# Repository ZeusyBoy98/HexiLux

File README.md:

# HexiLux
Made for Hack Club Fallout.

## Zine

## What does it do?
A custom open-source smart lighting solution, using tiling hexagonal panels. Featuring music sync and home assistant compatibility. 

## Why/Motivation?
Because I enjoy DJing and music reactive lights to go behind my setup would be really cool and elevate my experience.

## How?
In order to make this project for yourself, you'll need to purchase/3D print the items in the bill of materials below.

| Quantity | Item               | URL                                                                                                                                                                                                                                    | Unit Price ($USD)   | Total Price ($USD)  |
| -------- | ------------------ | -------------------------------------------------------------------------------------------------------------------------------------------------------------------------------------------------------------------------------------- | ------------------- | ------------------- |
| 1        | Microphone         | [Zaitronics](https://zaitronics.com.au/products/inmp441-i2s-mems-omnidirectional-microphone?variant=51395922100516&country=AU&currency=AUD&utm_medium=product_sync&utm_source=google&utm_content=sag_organic&utm_campaign=sag_organic) | 5.57                | 5.57                |
| 3        | Neopixel (10 pack) | [DigiKey](https://www.digikey.com.au/en/products/detail/adafruit-industries-llc/1655/5154679)                                                                                                                                          | 4.50                | 13.50               |
| 1        | Button             | [DigiKey](https://www.digikey.com.au/en/products/detail/omron-electronics-inc-emc-div/B3F-4050/95200)                                                                                                                                  | 0.52                | 0.52                |
| 1        | Board<br>          | [DigiKey](https://www.digikey.com.au/en/products/detail/seeed-technology-co-ltd/113991114/19285530)                                                                                                                                    | 7.49                | 7.49                |
| 4        | 100nF Capacitor    | [DigiKey](https://www.digikey.com.au/en/products/detail/vishay-beyschlag-draloric-bc-components/K104K15X7RF5TL2/286538)                                                                                                                | 0.28                | 1.12                |
| 1        | 330 Resistor       | [DigiKey](https://www.digikey.com.au/en/products/detail/yageo/FMP200JR-52-330R/2058682)                                                                                                                                                | 0.19                | 0.19                |
| 1        | 10k Resistor       | [DigiKey](https://www.digikey.com.au/en/products/detail/yageo/FMP200JR-52-10K/2058646)                                                                                                                                                 | 0.19                | 0.19                |
| 2        | 5.1k Resistor      | [DigiKey](https://www.digikey.com.au/en/products/detail/yageo/RC0603FR-075K1L/727268)                                                                                                                                                  | 0.10                | 0.20                |
| 1        | 47uF Capacitor     | [DigiKey](https://www.digikey.com.au/en/products/detail/tdk/FK20X5R0J476MN000/2815373)                                                                                                                                                 | 0.86                | 0.86                |
| 1        | 100uF Capacitor    | [DigiKey](https://www.digikey.com.au/en/products/detail/murata-electronics/GRM31CD80J107MEA8L/13904781)                                                                                                                                | 0.44                | 0.44                |
| 1        | Level Shifter      | [DigiKey](https://www.digikey.com.au/en/products/detail/texas-instruments/SN74AHCT1G125DBVR/376028)                                                                                                                                    | 0.14                | 0.14                |
| 1        | USBC               | [DigiKey](https://www.digikey.com.au/en/products/detail/amphenol-cs-fci/10155435-00011LF/11602060)                                                                                                                                     | 0.85                | 0.85                |
|          | Case               | 3D print files in /CAD                                                                                                                                                                                                                 | (3D printing: 1.17) | (3D printing: 1.17) |
| PCB      |                    |                                                                                                                                                                                                                                        |                     | 29.24               |
| Shipping |                    |                                                                                                                                                                                                                                        |                     | 3.70+20+9.52=33.22  |
| Total    |                    |                                                                                                                                                                                                                                        |                     | 93.53               |

### Build Guide:

#### 1. Preparation
Before starting, make sure you have:
<ul>
<li>All components from the BOM
<li>A soldering iron + solder
<li>Tweezers (there are lots of small components)
<li>Flux (helpful)
<li>A 3D printer (or get the printed parts from someone else)
<li>A USB-C cable
<li>A USB-C power adapter
</ul>

#### 2. Soldering
Take your pcb and begin soldering components to it<br>
Wiring schematic:

Recommended order:
<ul>
<li>SMD Components (resistors/capacitors, neopixels, logic converters)
<li>Microcontroller (Seeed XIAO ESP32-S3)
<li>Through-hole components (resistors/capacitors, buttons, microphone)
</ul>

#### 3. Case
<ul>
<li>3D print the case bottom and top.
<li>Place the PCB into the case bottom
<li>Snap on the case top
</ul>

#### 4. Firmware
<ul>
<li>Plug the middle USB-C port (ESP32-S3) into a computer
<li>Go to https://install.wled.me/
<li>Install the WLED firmware to the board
<li>Unplug
<li>Plug a power adapter into the off-centre USB-C port
<li>Follow the instructions here to start using: https://kno.wled.ge/basics/getting-started/
</ul>

Enjoy your HexiLux panel!

## Renders

## Designing

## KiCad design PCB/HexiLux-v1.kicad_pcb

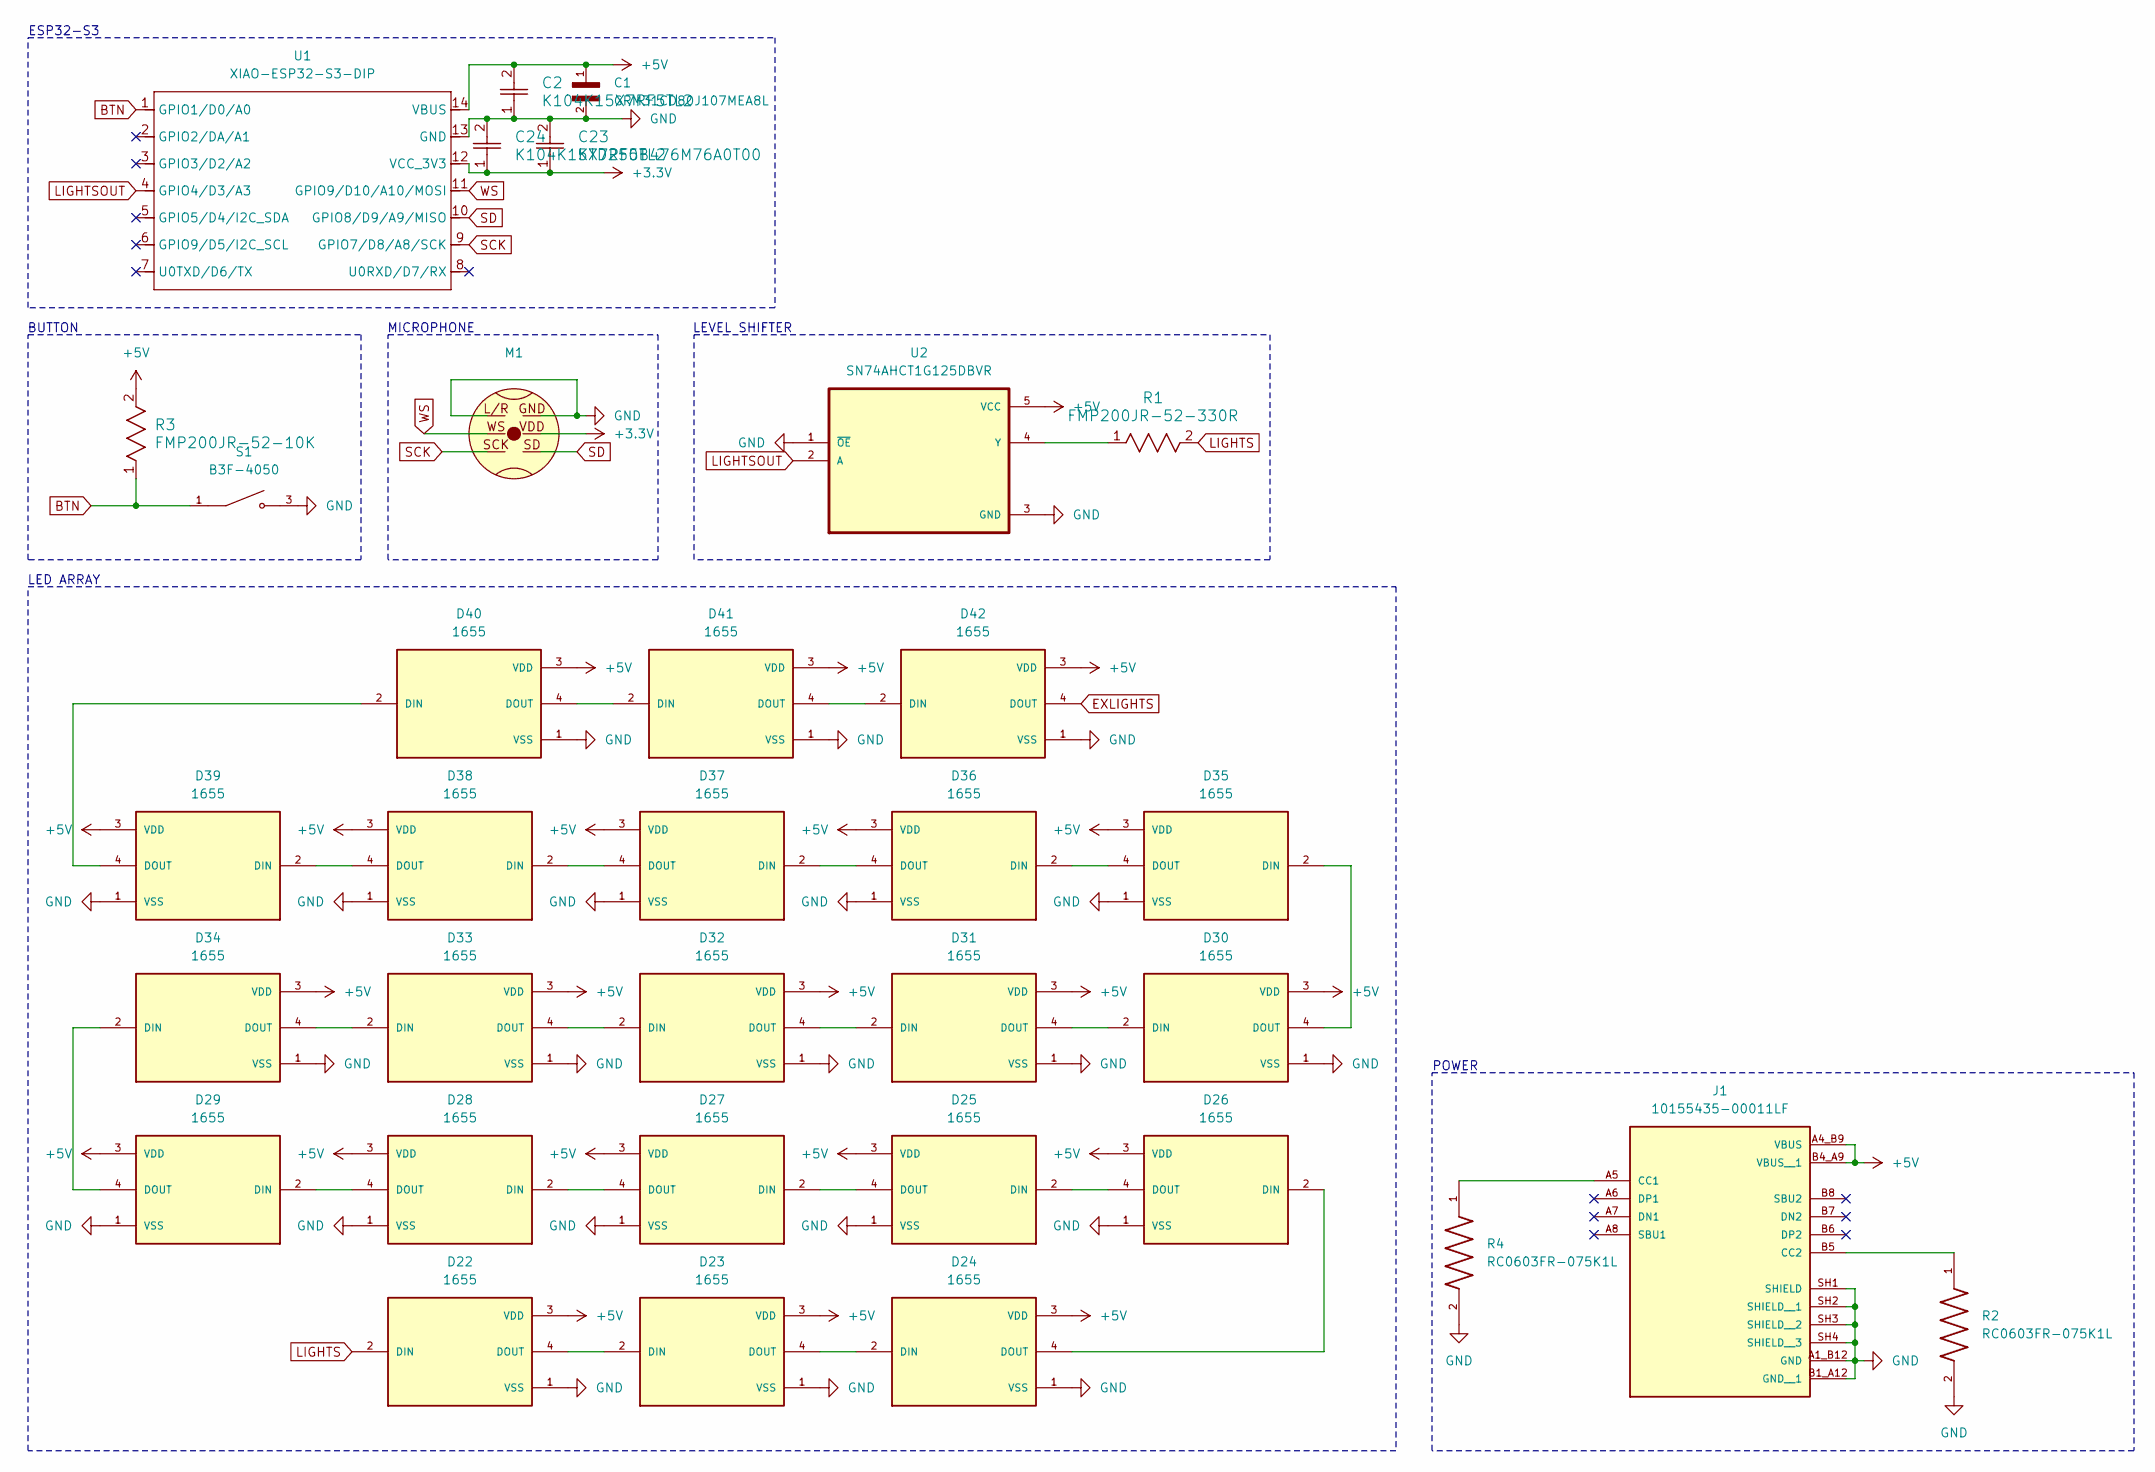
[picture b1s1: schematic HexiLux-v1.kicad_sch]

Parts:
C1: GRM31CD80J107MEA8L; 100uf_5V_1206; DigiKey_Part_Number 490-GRM31CD80J107MEA8LCT-ND
C2, C24: K104K15X7RF5TL2; K104K15X7RF5TL2_VIS
C23: KTD250B476M76A0T00; CAP_NTD_76_05.5T_NIP
D22, D23, D24, D25, D26, D27, D28, D29, D30, D31, D32, D33, D34, D35, D36, D37, D38, D39, D40, D41, D42: 1655; LED_1655_5050_neopixel; PARTREV 01
J1: 10155435-00011LF; AMPHENOL_10155435-00011LF; PARTREV C
M1: INMP441
R1: FMP200JR-52-330R; YAG_FMP200_YAG_52_330k
R2, R4: RC0603FR-075K1L; 5.1k_0603_DK
R3: FMP200JR-52-10K; YAG_FMP200_YAG
S1: B3F-4050; SW_B3F-4050; DigiKey_Part_Number SW413-ND
U1: XIAO-ESP32-S3-DIP
U2: SN74AHCT1G125DBVR; 74AHCT_level_shifter

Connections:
+3.3V: C23.1, C24.1, M1.VDD, U1.12 (VCC_3V3)
+5V: C1.1, C2.2, D22.3 (VDD), D23.3 (VDD), D24.3 (VDD), D25.3 (VDD), D26.3 (VDD), D27.3 (VDD), D28.3 (VDD), D29.3 (VDD), D30.3 (VDD), D31.3 (VDD), D32.3 (VDD), D33.3 (VDD), D34.3 (VDD), D35.3 (VDD), D36.3 (VDD), D37.3 (VDD), D38.3 (VDD), D39.3 (VDD), D40.3 (VDD), D41.3 (VDD), D42.3 (VDD), J1.A4_B9 (VBUS), J1.B4_A9 (VBUS__1), R3.2, U1.14 (VBUS), U2.5 (VCC)
BTN: R3.1, S1.1, S1.2, U1.1 (GPIO1/D0/A0)
EXLIGHTS: D42.4 (DOUT)
GND: C1.2, C2.1, C23.2, C24.2, D22.1 (VSS), D23.1 (VSS), D24.1 (VSS), D25.1 (VSS), D26.1 (VSS), D27.1 (VSS), D28.1 (VSS), D29.1 (VSS), D30.1 (VSS), D31.1 (VSS), D32.1 (VSS), D33.1 (VSS), D34.1 (VSS), D35.1 (VSS), D36.1 (VSS), D37.1 (VSS), D38.1 (VSS), D39.1 (VSS), D40.1 (VSS), D41.1 (VSS), D42.1 (VSS), J1.A1_B12 (GND), J1.B1_A12 (GND__1), J1.SH1 (SHIELD), J1.SH2 (SHIELD__1), J1.SH3 (SHIELD__2), J1.SH4 (SHIELD__3), M1.GND, M1.L/R, R2.2, R4.2, S1.3, S1.4, U1.13 (GND), U2.1 (~OE), U2.3 (GND)
LIGHTS: D22.2 (DIN), R1.2
LIGHTSOUT: U1.4 (GPIO4/D3/A3), U2.2 (A)
unnamed: D22.4 (DOUT), D23.2 (DIN)
unnamed: D23.4 (DOUT), D24.2 (DIN)
unnamed: D24.4 (DOUT), D26.2 (DIN)
unnamed: D25.2 (DIN), D26.4 (DOUT)
unnamed: D25.4 (DOUT), D27.2 (DIN)
unnamed: D27.4 (DOUT), D28.2 (DIN)
unnamed: D28.4 (DOUT), D29.2 (DIN)
unnamed: D29.4 (DOUT), D34.2 (DIN)
unnamed: D30.2 (DIN), D31.4 (DOUT)
unnamed: D30.4 (DOUT), D35.2 (DIN)
unnamed: D31.2 (DIN), D32.4 (DOUT)
unnamed: D32.2 (DIN), D33.4 (DOUT)
unnamed: D33.2 (DIN), D34.4 (DOUT)
unnamed: D35.4 (DOUT), D36.2 (DIN)
unnamed: D36.4 (DOUT), D37.2 (DIN)
unnamed: D37.4 (DOUT), D38.2 (DIN)
unnamed: D38.4 (DOUT), D39.2 (DIN)
unnamed: D39.4 (DOUT), D40.2 (DIN)
unnamed: D40.4 (DOUT), D41.2 (DIN)
unnamed: D41.4 (DOUT), D42.2 (DIN)
unnamed: J1.A5 (CC1), R4.1
unnamed: J1.B5 (CC2), R2.1
unnamed: R1.1, U2.4 (Y)
SCK: M1.SCK, U1.9 (GPIO7/D8/A8/SCK)
SD: M1.SD, U1.10 (GPIO8/D9/A9/MISO)
WS: M1.WS, U1.11 (GPIO9/D10/A10/MOSI)

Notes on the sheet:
POWER
LED ARRAY
BUTTON
MICROPHONE
ESP32-S3
LEVEL SHIFTER

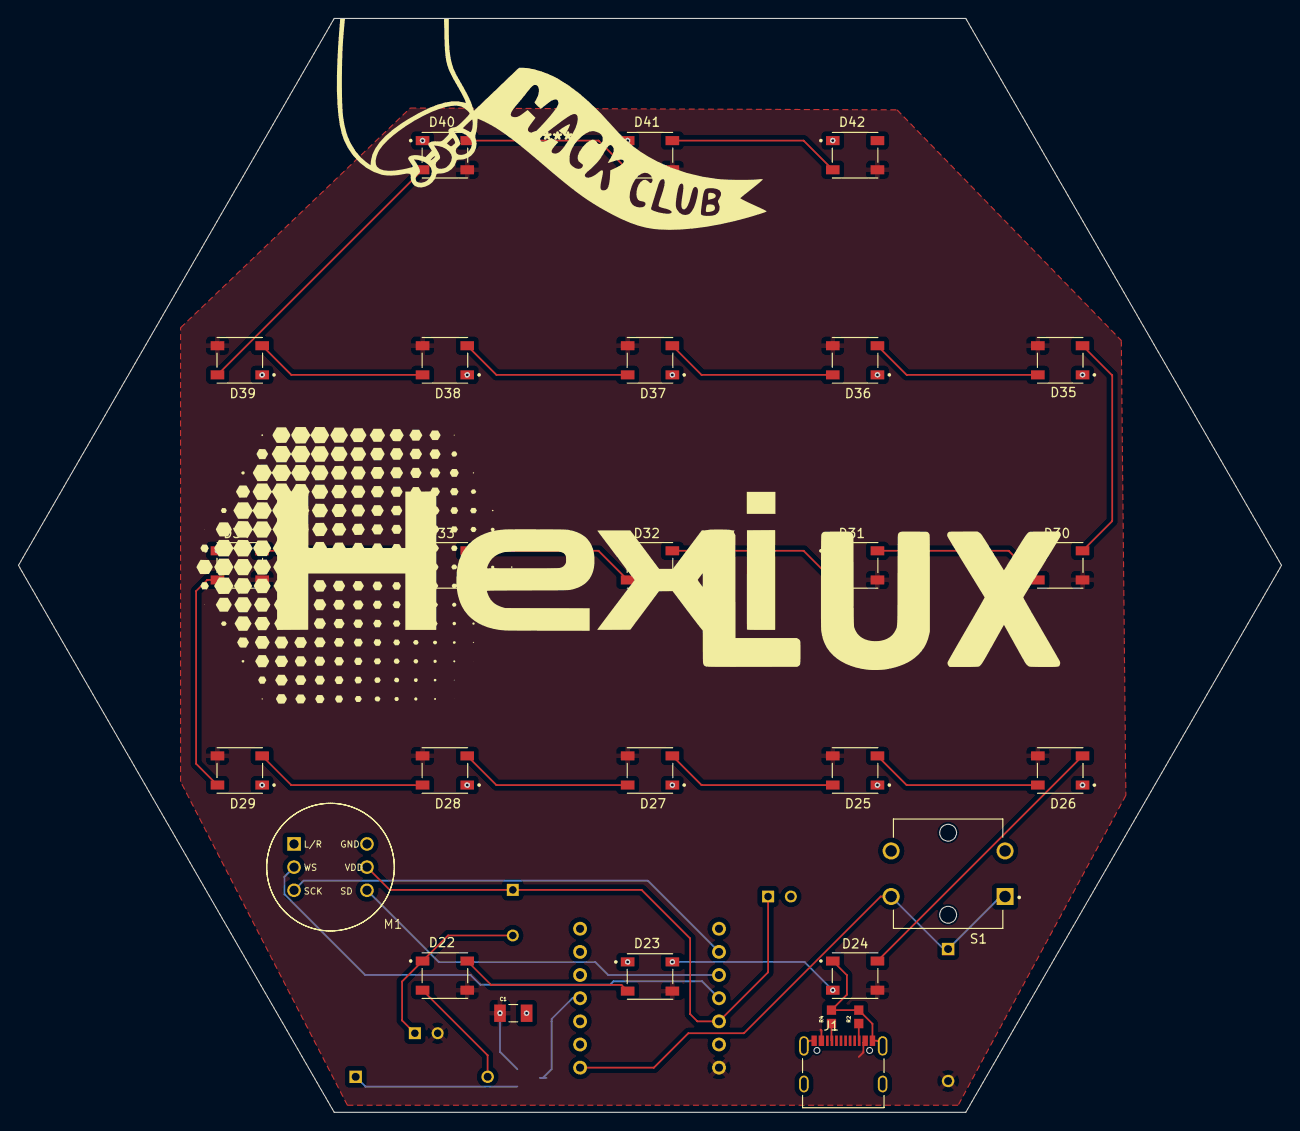
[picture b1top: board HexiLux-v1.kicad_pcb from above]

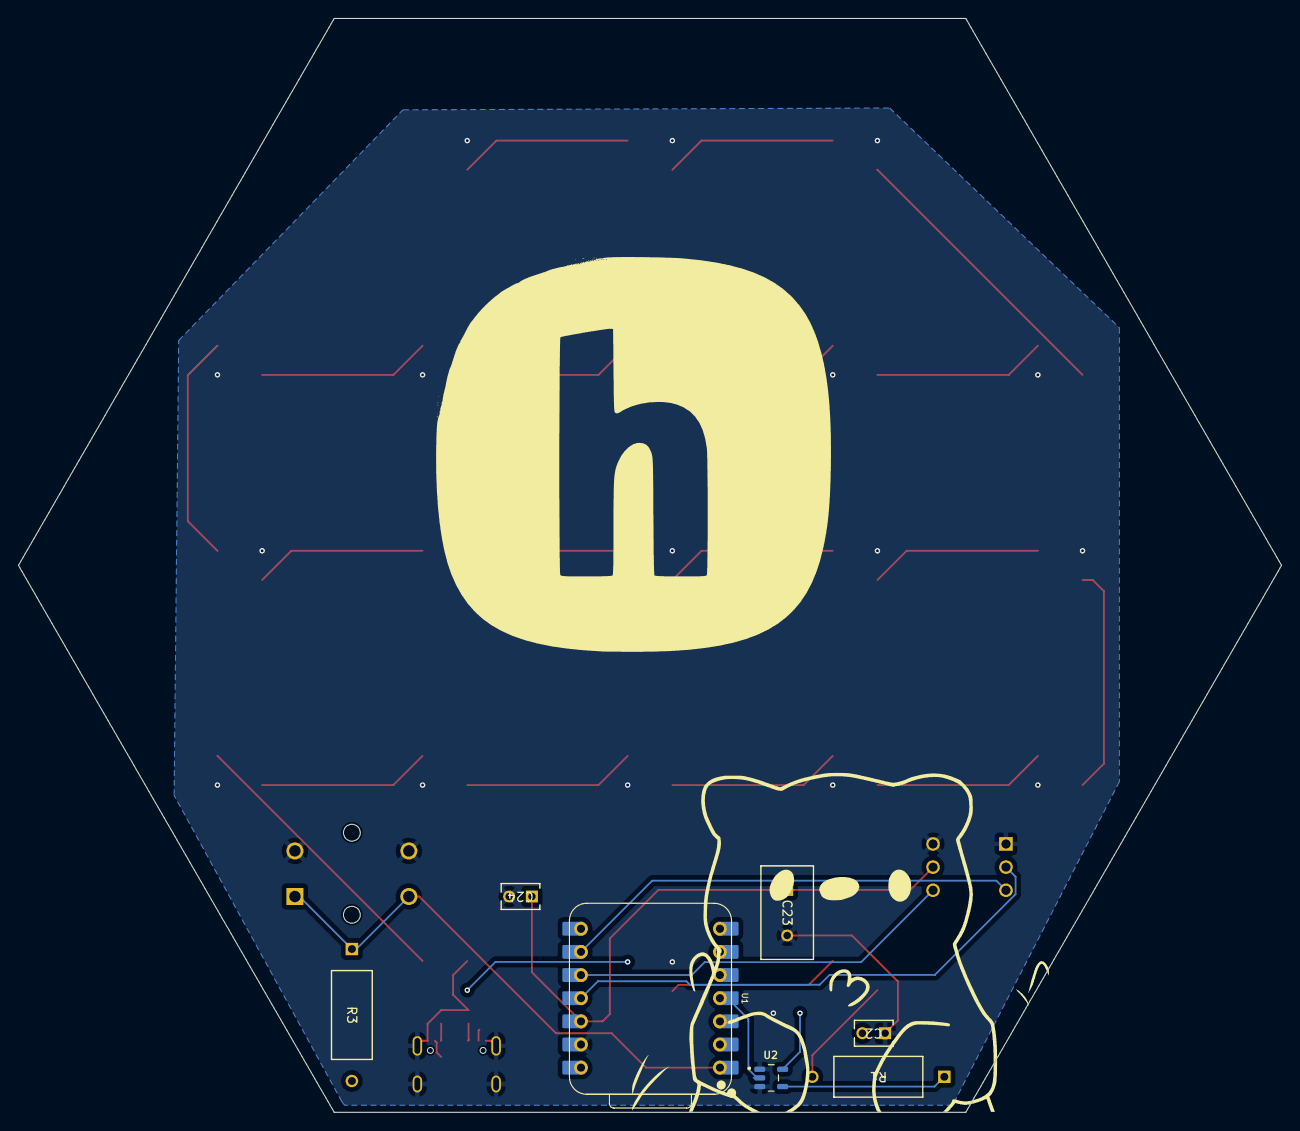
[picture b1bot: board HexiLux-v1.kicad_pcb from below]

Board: 2 copper layers, 138.6 x 120.0 mm, 34 parts (7 on the bottom side), 32 nets.

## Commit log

2026-03-21 Add PCB files
2026-04-24 Start work on CAD
2026-04-25 Export CAD files & finish BOM
2026-04-25 Fixing gerbers
2026-04-25 Readd gerbers
2026-04-25 Add Zine
2026-04-25 Add wiring schematic to build guide
